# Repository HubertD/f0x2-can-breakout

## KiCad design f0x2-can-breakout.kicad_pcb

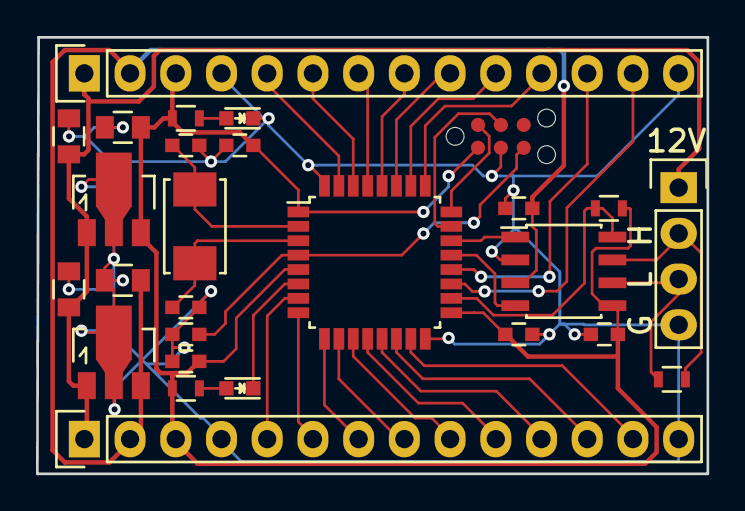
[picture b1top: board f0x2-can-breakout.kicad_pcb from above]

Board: 2 copper layers, 37.2 x 24.2 mm, 27 parts (0 on the bottom side), 35 nets.

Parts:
C1, C2: 18pF; C_0603
C3, C4, C5, C6, C11, C12: 100nF; C_0603
C7, C8, C9, C10: 10uF; C_0805
D1: green; LED_0603
D2: red; LED_0603
P1, P2: CONN_01X14; Pin_Header_Straight_1x14
P3: CONN_01X04; Pin_Header_Straight_1x04
R1: 10K; R_0603
R2, R3: 1K; R_0603
R4: dnp; R_0603
U1: STM32F042K6Tx; LQFP-32_7x7mm_Pitch0.8mm
U2: MCP1754ST-3302E/MB; SOT89-3_Housing
U3: MCP1754ST-5002E/MB; SOT89-3_Housing
U4: TJA1051T/3; SOIC-8_3.9x4.9mm_Pitch1.27mm
X1: CON_SWD; TC2030-NL
Y1: 8MHz; ABM3

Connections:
+3V3: C4.1, C5.1, C6.1, C9.1, C11.1, P1.3, P2.3, R1.1, R2.1, R3.1, U1.1, U1.5, U1.17, U2.3, U4.5, X1.1
+5V: C10.1, C12.1, P1.2, P2.2, U3.3, U4.3
+12V: C7.1, C8.1, P1.1, P2.1, P3.1, U2.1, U3.1
CAN_H: P3.2, R4.1, U4.7
CAN_L: P3.3, R4.2, U4.6
CAN_RXD: U1.21, U4.4
CAN_S: R1.2, U1.18, U4.8
CAN_TXD: U1.22, U4.1
GND: C1.2, C2.2, C3.2, C4.2, C5.2, C6.2, C7.2, C8.2, C9.2, C10.2, C11.2, C12.2, D1.1, P1.4, P1.14, P2.4, P2.14, P3.4, U1.16, U1.32, U2.2, U3.2, U4.2, X1.3
NRST: C3.1, U1.4, X1.5
unnamed: C1.1, U1.2, Y1.1
unnamed: C2.1, U1.3, Y1.2
unnamed: D1.2, R2.2
unnamed: D2.2, R3.2
PA1: P1.5, U1.7
PA2: P1.6, U1.8
PA3: P1.7, U1.9
PA4: P1.8, U1.10
PA5: P1.9, U1.11
PA6: P1.10, U1.12
PA7: P1.11, U1.13
PA9: P2.13, U1.19
PA10: P2.12, U1.20
PA15: P2.11, U1.25
PB0: P1.12, U1.14
PB1: P1.13, U1.15
PB3: P2.10, U1.26
PB4: P2.9, U1.27
PB5: P2.8, U1.28
PB6: P2.7, U1.29
PB7: P2.6, U1.30
PB8: P2.5, U1.31
SWCLK: U1.24, X1.2
SWDIO: U1.23, X1.4
USR_LED: D2.1, U1.6

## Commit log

2016-06-26 initial checkin
